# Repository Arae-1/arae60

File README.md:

These are the design files for the arae60 keyboard. They will be updated as I move along the project

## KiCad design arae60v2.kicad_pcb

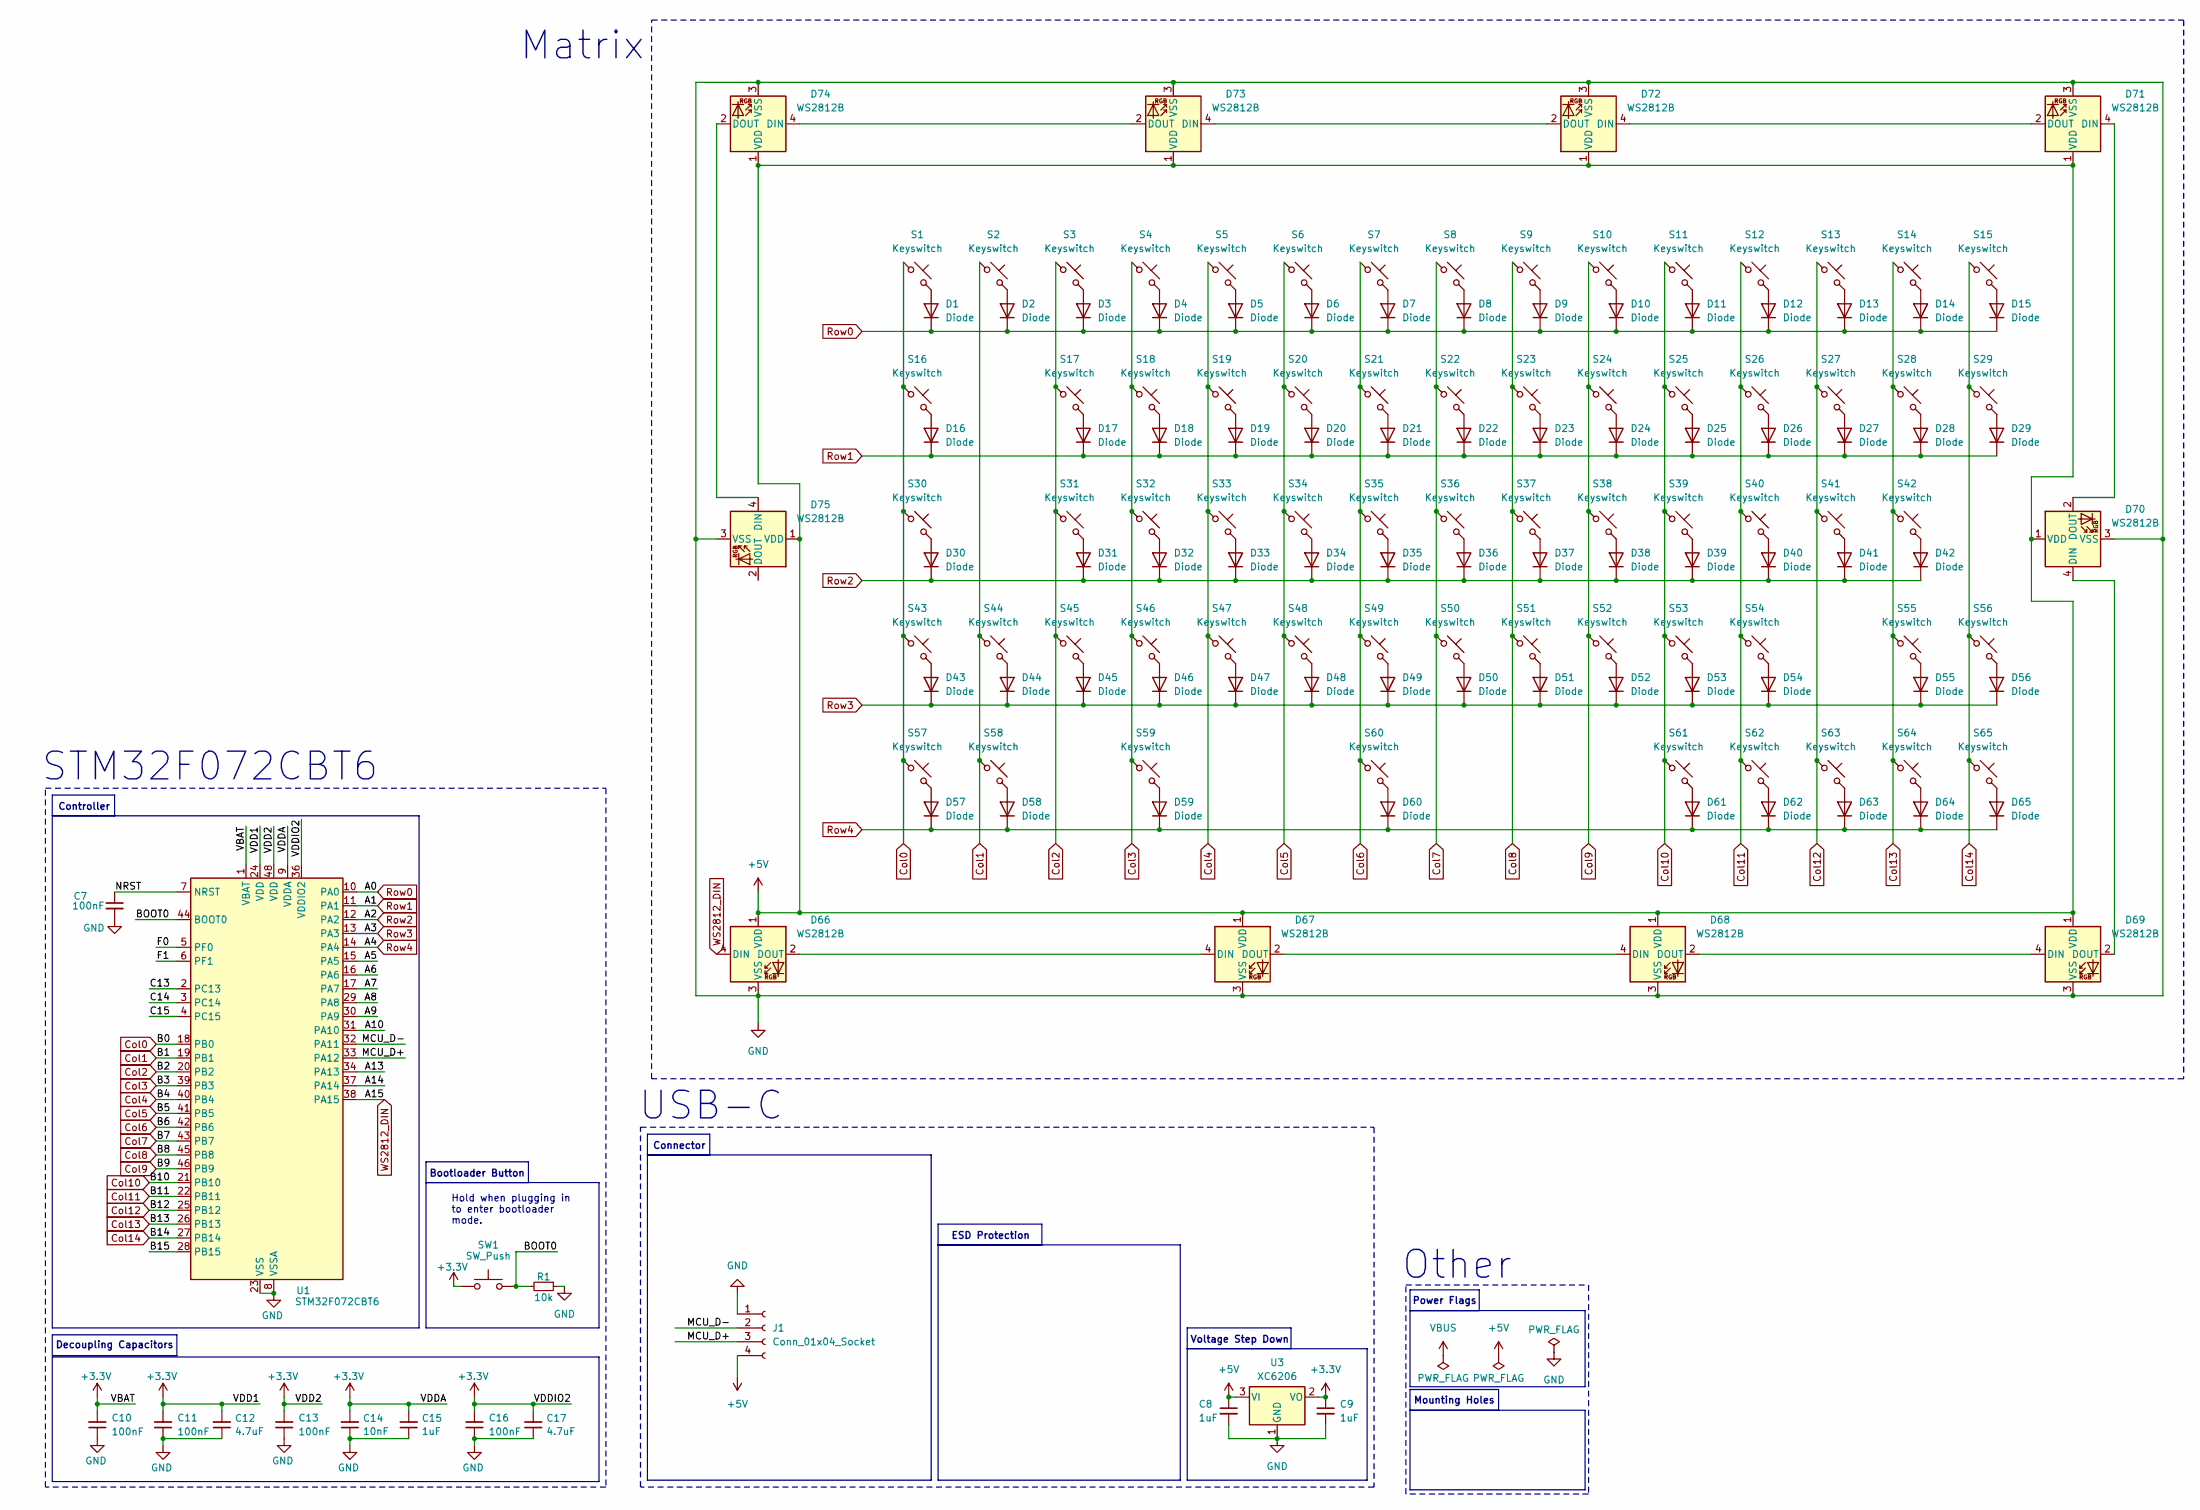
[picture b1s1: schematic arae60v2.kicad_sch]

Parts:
C7: 100nF; Capacitor_0402; LCSC C307331
C8, C9: 1uF; Capacitor_0402; LCSC C52923
C10, C11, C13, C16: 100nF; Capacitor_0402; MPN CL05B104KB54PNC; LCSC C307331
C12, C17: 4.7uF; Capacitor_0402; MPN CL05A475MP5NRNC; LCSC C23733
C14: 10nF; Capacitor_0402; MPN CL05B103KB5NNNC; LCSC C15195
C15: 1uF; Capacitor_0402; MPN CL05A105KA5NQNC; LCSC C52923
D1, D2, D3, D4, D5, D6, D7, D8, D9, D10, D11, D12, D13, D14, D15, D16, D17, D18, D19, D20, D21, D22, D23, D24, D25, D26, D27, D28, D29, D30, D31, D32, D33, D34, D35, D36, D37, D38, D39, D40, D41, D42, D43, D44, D45, D46, D47, D48, D49, D50, D51, D52, D53, D54, D55, D56, D57, D58, D59, D60, D61, D62, D63, D64, D65: Diode; Diode_SOD-123
D66, D67, D68, D69, D70, D71, D72, D73, D74, D75: WS2812B; LED_WS2812B_PLCC4_5.0x5.0mm_P3.2mm
J1: Conn_01x04_Socket; JST_SH_SM04B-SRSS-TB_1x04-1MP_P1.00mm_Horizontal
R1: 10k; Resistor_0402; LCSC C25744
S1, S2, S3, S4, S5, S6, S7, S8, S9, S10, S11, S12, S13, S14, S15, S17, S18, S19, S20, S21, S22, S23, S24, S25, S26, S27, S28, S31, S32, S33, S34, S35, S36, S37, S38, S39, S40, S41, S43, S45, S46, S47, S48, S49, S50, S51, S52, S53, S54, S56, S61, S62, S63, S64, S65: Keyswitch; Hotswap_MX_1.00u
S16, S29: Keyswitch; Hotswap_MX_1.50u
S30, S55: Keyswitch; Hotswap_MX_1.75u
S42: Keyswitch; Hotswap_MX_2.25u
S44, S57, S58, S59: Keyswitch; Hotswap_MX_1.25u
S60: Keyswitch; Hotswap_MX_6.25u
SW1: SW_Push; Button_TL3342; LCSC C115351
U1: STM32F072CBT6; Package_LQFP-48_7x7mm_P0.5; LCSC C81720
U3: XC6206; Voltage_SOT-23; LCSC C5446

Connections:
+3.3V: C9.1, C10.2, C11.2, C12.2, C13.2, C14.2, C15.2, C16.2, C17.2, SW1.1, U1.1 (VBAT), U1.9 (VDDA), U1.24 (VDD), U1.36 (VDDIO2), U1.48 (VDD), U3.2 (VO)
+5V: C8.1, D66.1 (VDD), D67.1 (VDD), D68.1 (VDD), D69.1 (VDD), D70.1 (VDD), D71.1 (VDD), D72.1 (VDD), D73.1 (VDD), D74.1 (VDD), D75.1 (VDD), J1.4, U3.3 (VI)
/A5: U1.15 (PA5)
/A6: U1.16 (PA6)
/A7: U1.17 (PA7)
/A8: U1.29 (PA8)
/A9: U1.30 (PA9)
/A10: U1.31 (PA10)
/A13: U1.34 (PA13)
/A14: U1.37 (PA14)
/B15: U1.28 (PB15)
/BOOT0: R1.2, SW1.2, U1.44 (BOOT0)
/C13: U1.2 (PC13)
/C14: U1.3 (PC14)
/C15: U1.4 (PC15)
/F0: U1.5 (PF0)
/F1: U1.6 (PF1)
/MCU_D+: J1.3, U1.33 (PA12)
/MCU_D-: J1.2, U1.32 (PA11)
/NRST: C7.1, U1.7 (NRST)
Col0: S1.1, S16.1, S30.1, S43.1, S57.1, U1.18 (PB0)
Col1: S2.1, S44.1, S58.1, U1.19 (PB1)
Col2: S3.1, S17.1, S31.1, S45.1, U1.20 (PB2)
Col3: S4.1, S18.1, S32.1, S46.1, S59.1, U1.39 (PB3)
Col4: S5.1, S19.1, S33.1, S47.1, U1.40 (PB4)
Col5: S6.1, S20.1, S34.1, S48.1, U1.41 (PB5)
Col6: S7.1, S21.1, S35.1, S49.1, S60.1, U1.42 (PB6)
Col7: S8.1, S22.1, S36.1, S50.1, U1.43 (PB7)
Col8: S9.1, S23.1, S37.1, S51.1, U1.45 (PB8)
Col9: S10.1, S24.1, S38.1, S52.1, U1.46 (PB9)
Col10: S11.1, S25.1, S39.1, S53.1, S61.1, U1.21 (PB10)
Col11: S12.1, S26.1, S40.1, S54.1, S62.1, U1.22 (PB11)
Col12: S13.1, S27.1, S41.1, S63.1, U1.25 (PB12)
Col13: S14.1, S28.1, S42.1, S55.1, S64.1, U1.26 (PB13)
Col14: S15.1, S29.1, S56.1, S65.1, U1.27 (PB14)
GND: C7.2, C8.2, C9.2, C10.1, C11.1, C12.1, C13.1, C14.1, C15.1, C16.1, C17.1, D66.3 (VSS), D67.3 (VSS), D68.3 (VSS), D69.3 (VSS), D70.3 (VSS), D71.3 (VSS), D72.3 (VSS), D73.3 (VSS), D74.3 (VSS), D75.3 (VSS), J1.1, R1.1, U1.8 (VSSA), U1.23 (VSS), U1.35 (VSS), U1.47 (VSS), U3.1 (GND)
unnamed: D1.2 (A), S1.2
unnamed: D2.2 (A), S2.2
unnamed: D3.2 (A), S3.2
unnamed: D4.2 (A), S4.2
unnamed: D5.2 (A), S5.2
unnamed: D6.2 (A), S6.2
unnamed: D7.2 (A), S7.2
unnamed: D8.2 (A), S8.2
unnamed: D9.2 (A), S9.2
unnamed: D10.2 (A), S10.2
unnamed: D11.2 (A), S11.2
unnamed: D12.2 (A), S12.2
unnamed: D13.2 (A), S13.2
unnamed: D14.2 (A), S14.2
unnamed: D15.2 (A), S15.2
unnamed: D16.2 (A), S16.2
unnamed: D17.2 (A), S17.2
unnamed: D18.2 (A), S18.2
unnamed: D19.2 (A), S19.2
unnamed: D20.2 (A), S20.2
unnamed: D21.2 (A), S21.2
unnamed: D22.2 (A), S22.2
unnamed: D23.2 (A), S23.2
unnamed: D24.2 (A), S24.2
unnamed: D25.2 (A), S25.2
unnamed: D26.2 (A), S26.2
unnamed: D27.2 (A), S27.2
unnamed: D28.2 (A), S28.2
unnamed: D29.2 (A), S29.2
unnamed: D30.2 (A), S30.2
unnamed: D31.2 (A), S31.2
unnamed: D32.2 (A), S32.2
unnamed: D33.2 (A), S33.2
unnamed: D34.2 (A), S34.2
unnamed: D35.2 (A), S35.2
unnamed: D36.2 (A), S36.2
unnamed: D37.2 (A), S37.2
unnamed: D38.2 (A), S38.2
unnamed: D39.2 (A), S39.2
unnamed: D40.2 (A), S40.2
unnamed: D41.2 (A), S41.2
unnamed: D42.2 (A), S42.2
unnamed: D43.2 (A), S43.2
unnamed: D44.2 (A), S44.2
unnamed: D45.2 (A), S45.2
unnamed: D46.2 (A), S46.2
unnamed: D47.2 (A), S47.2
unnamed: D48.2 (A), S48.2
unnamed: D49.2 (A), S49.2
unnamed: D50.2 (A), S50.2
unnamed: D51.2 (A), S51.2
unnamed: D52.2 (A), S52.2
unnamed: D53.2 (A), S53.2
unnamed: D54.2 (A), S54.2
unnamed: D55.2 (A), S55.2
unnamed: D56.2 (A), S56.2
unnamed: D57.2 (A), S57.2
unnamed: D58.2 (A), S58.2
unnamed: D59.2 (A), S59.2
unnamed: D60.2 (A), S60.2
unnamed: D61.2 (A), S61.2
unnamed: D62.2 (A), S62.2
unnamed: D63.2 (A), S63.2
unnamed: D64.2 (A), S64.2
unnamed: D65.2 (A), S65.2
unnamed: D66.2 (DOUT), D67.4 (DIN)
unnamed: D67.2 (DOUT), D68.4 (DIN)
unnamed: D68.2 (DOUT), D69.4 (DIN)
unnamed: D69.2 (DOUT), D70.4 (DIN)
unnamed: D70.2 (DOUT), D71.4 (DIN)
unnamed: D71.2 (DOUT), D72.4 (DIN)
unnamed: D72.2 (DOUT), D73.4 (DIN)
unnamed: D73.2 (DOUT), D74.4 (DIN)
unnamed: D74.2 (DOUT), D75.4 (DIN)
Row0: D1.1 (K), D2.1 (K), D3.1 (K), D4.1 (K), D5.1 (K), D6.1 (K), D7.1 (K), D8.1 (K), D9.1 (K), D10.1 (K), D11.1 (K), D12.1 (K), D13.1 (K), D14.1 (K), D15.1 (K), U1.10 (PA0)
Row1: D16.1 (K), D17.1 (K), D18.1 (K), D19.1 (K), D20.1 (K), D21.1 (K), D22.1 (K), D23.1 (K), D24.1 (K), D25.1 (K), D26.1 (K), D27.1 (K), D28.1 (K), D29.1 (K), U1.11 (PA1)
Row2: D30.1 (K), D31.1 (K), D32.1 (K), D33.1 (K), D34.1 (K), D35.1 (K), D36.1 (K), D37.1 (K), D38.1 (K), D39.1 (K), D40.1 (K), D41.1 (K), D42.1 (K), U1.12 (PA2)
Row3: D43.1 (K), D44.1 (K), D45.1 (K), D46.1 (K), D47.1 (K), D48.1 (K), D49.1 (K), D50.1 (K), D51.1 (K), D52.1 (K), D53.1 (K), D54.1 (K), D55.1 (K), D56.1 (K), U1.13 (PA3)
Row4: D57.1 (K), D58.1 (K), D59.1 (K), D60.1 (K), D61.1 (K), D62.1 (K), D63.1 (K), D64.1 (K), D65.1 (K), U1.14 (PA4)
WS2812_DIN: D66.4 (DIN), U1.38 (PA15)

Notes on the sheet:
Hold when plugging in to enter bootloader mode.
STM32F072CBT6
USB-C
Mounting Holes
Decoupling Capacitors
Controller
ESD Protection
Power Flags
Voltage Step Down
Other
Bootloader Button
Matrix
Connector

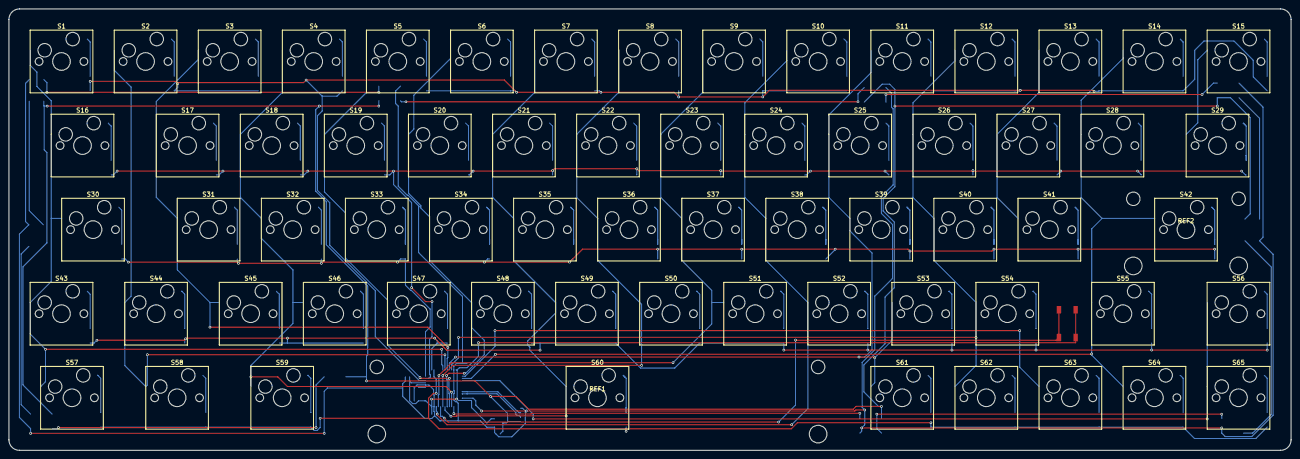
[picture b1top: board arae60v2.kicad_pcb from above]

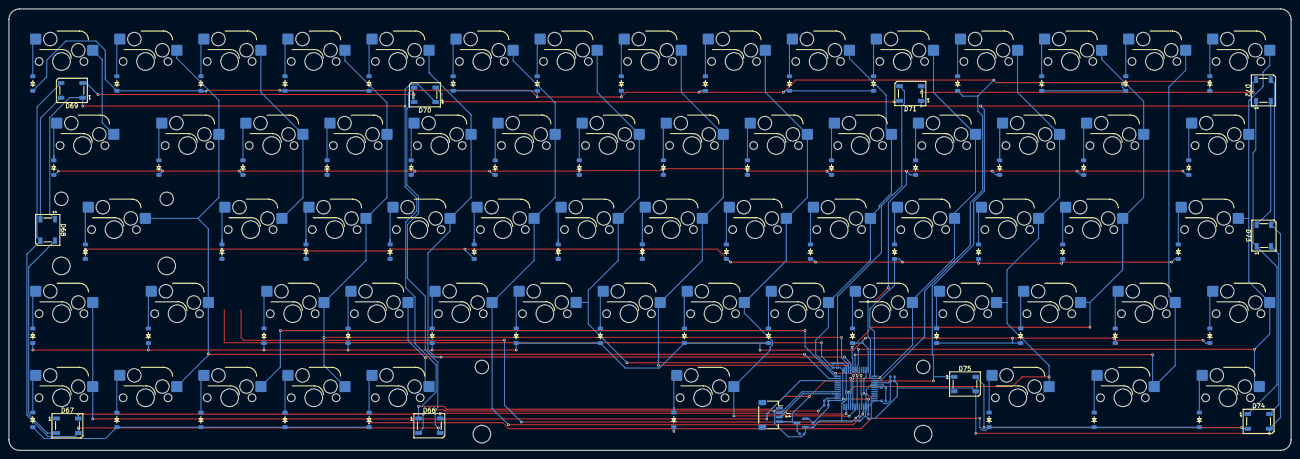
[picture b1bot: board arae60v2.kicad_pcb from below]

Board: 2 copper layers, 290.5 x 100.0 mm, 158 parts (90 on the bottom side), 102 nets.

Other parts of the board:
REF1: Stabilizer_MX_6.25u
REF2: Stabilizer_MX_2.00u

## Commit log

2025-01-24 Create README.md
    Added a README
2025-01-24 Create 1
2025-01-24 updated files to fix a few missing traces
2025-01-24 attempt to update files
    I have no clue how github works
